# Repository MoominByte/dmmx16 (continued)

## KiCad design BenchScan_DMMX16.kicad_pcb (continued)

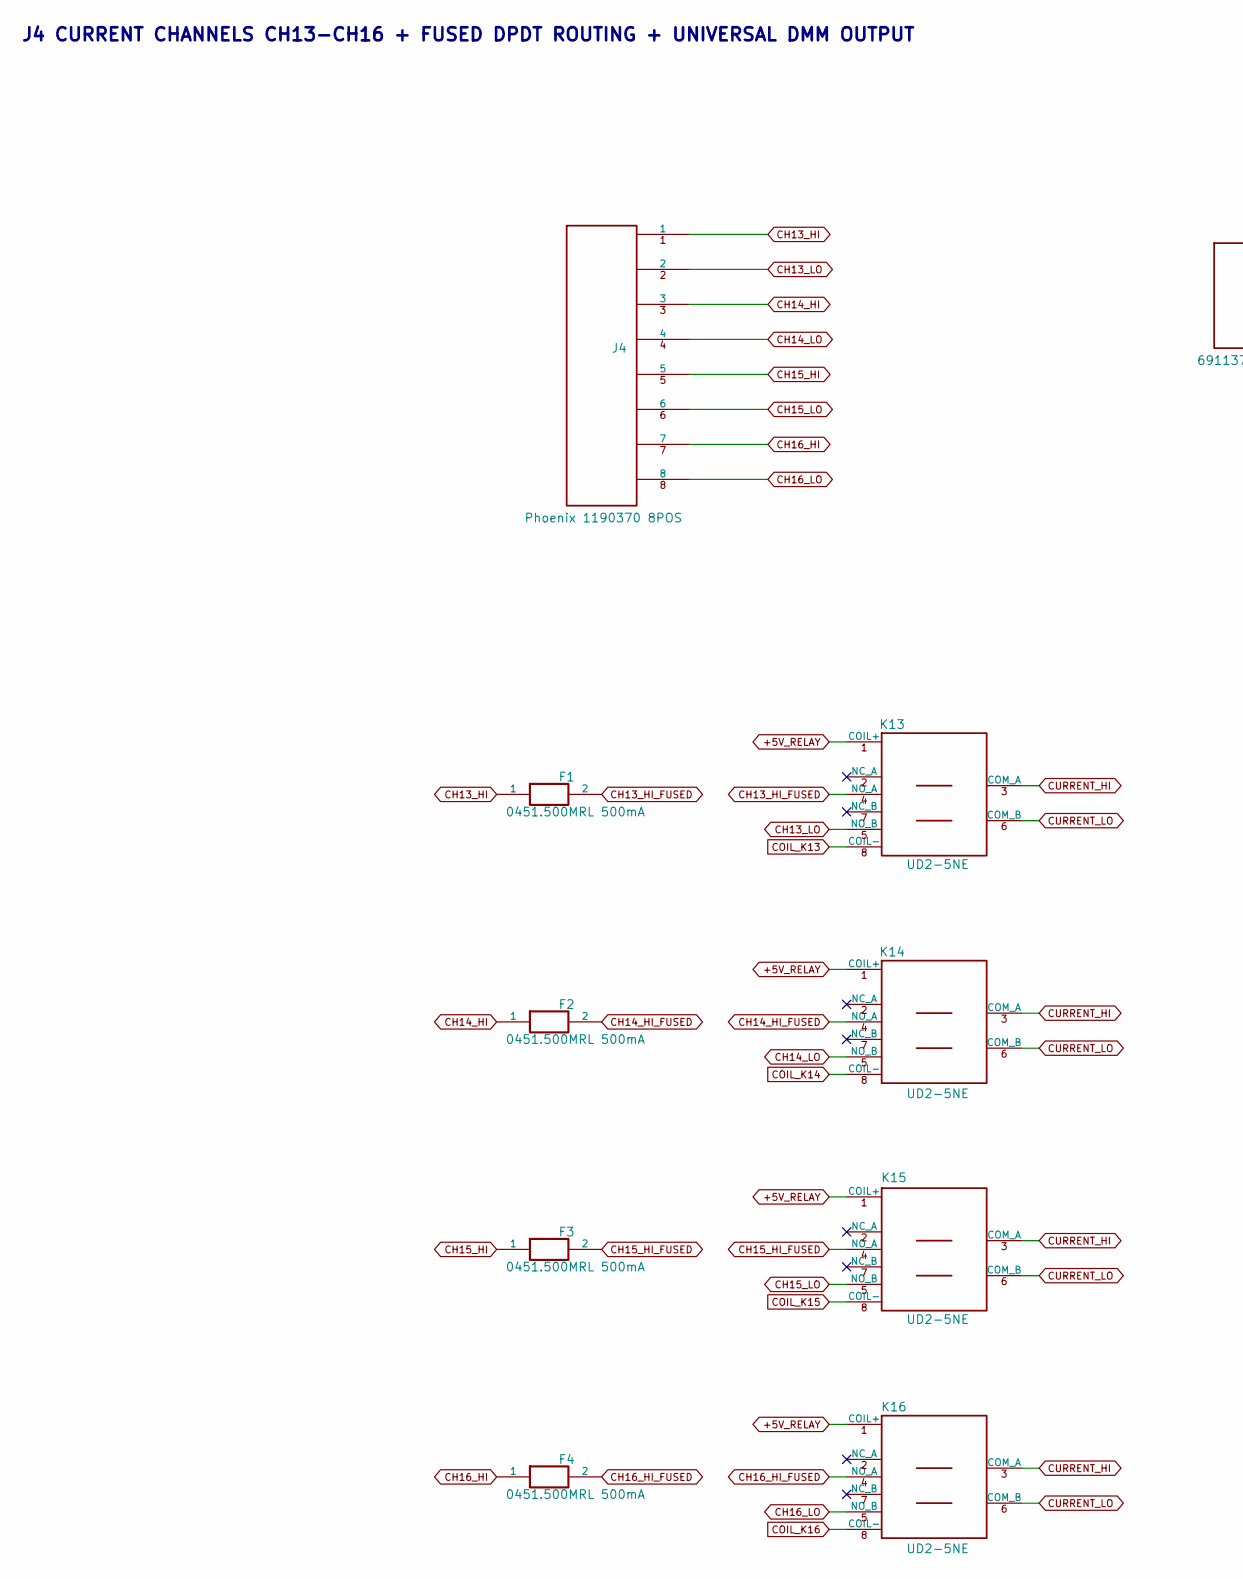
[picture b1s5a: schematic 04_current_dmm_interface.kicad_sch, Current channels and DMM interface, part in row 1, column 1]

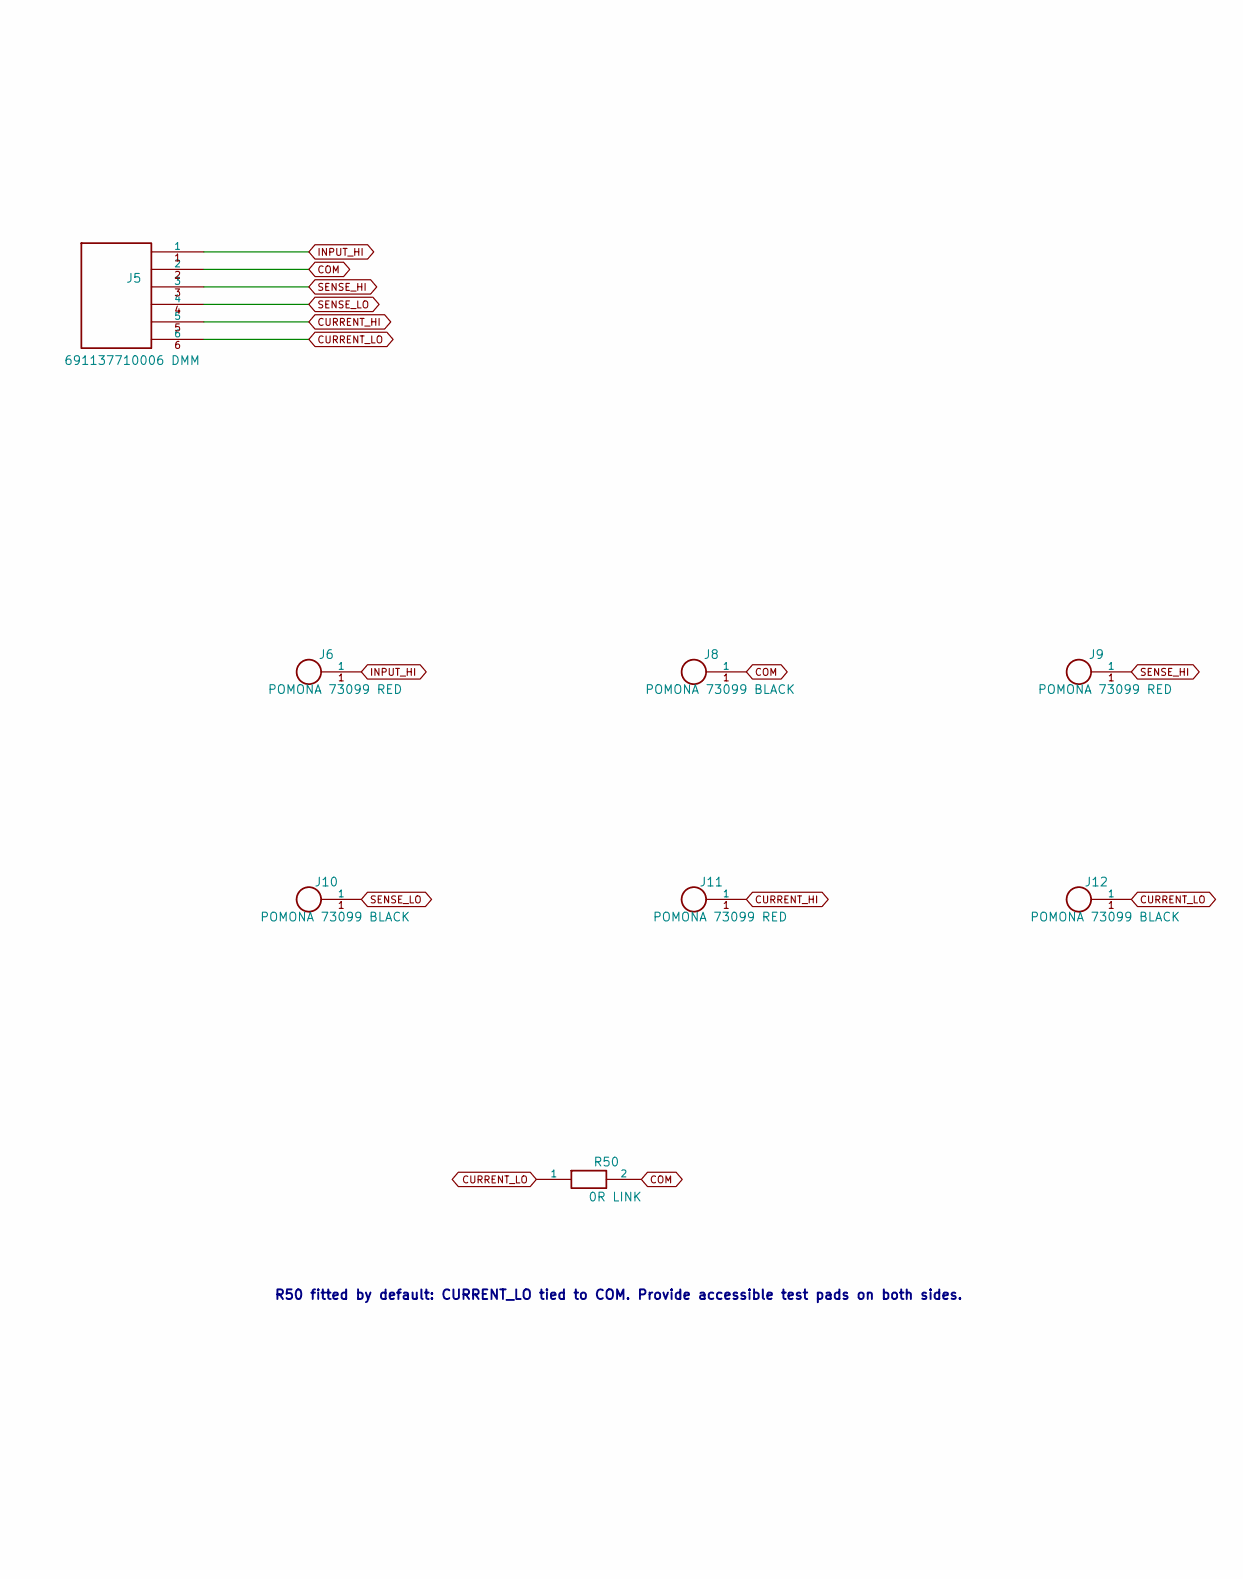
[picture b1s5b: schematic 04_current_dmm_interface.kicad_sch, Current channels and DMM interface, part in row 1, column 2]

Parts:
F1, F2, F3, F4: 0451.500MRL 500mA; Fuse_Littelfuse_0451_NANO2_2410
J4: Phoenix 1190370 8POS; Phoenix_1190370_LPTA-2.5-8-5.0_16THT_Paired
J5: 691137710006 DMM; J_Wurth_WR-TBL_691137710006
J6, J9, J11: POMONA 73099 RED; Pomona_73099_RightAngle_SafetyJack
J8, J10, J12: POMONA 73099 BLACK; Pomona_73099_RightAngle_SafetyJack
K13, K14, K15, K16: UD2-5NE; Relay_KEMET_UD2_NE
R50: 0R LINK; R_0805_2012Metric

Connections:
+5V_RELAY: K13.1 (COIL+), K14.1 (COIL+), K15.1 (COIL+), K16.1 (COIL+); also elsewhere on the board
CH13_HI: F1.1, J4.1
CH13_HI_FUSED: F1.2, K13.4 (NO_A)
CH13_LO: J4.2, K13.5 (NO_B)
CH14_HI: F2.1, J4.3
CH14_HI_FUSED: F2.2, K14.4 (NO_A)
CH14_LO: J4.4, K14.5 (NO_B)
CH15_HI: F3.1, J4.5
CH15_HI_FUSED: F3.2, K15.4 (NO_A)
CH15_LO: J4.6, K15.5 (NO_B)
CH16_HI: F4.1, J4.7
CH16_HI_FUSED: F4.2, K16.4 (NO_A)
CH16_LO: J4.8, K16.5 (NO_B)
COIL_K13: K13.8 (COIL-); also elsewhere on the board
COIL_K14: K14.8 (COIL-); also elsewhere on the board
COIL_K15: K15.8 (COIL-); also elsewhere on the board
COIL_K16: K16.8 (COIL-); also elsewhere on the board
COM: J5.2, J8.1, R50.2; also elsewhere on the board
CURRENT_HI: J5.5, J11.1, K13.3 (COM_A), K14.3 (COM_A), K15.3 (COM_A), K16.3 (COM_A)
CURRENT_LO: J5.6, J12.1, K13.6 (COM_B), K14.6 (COM_B), K15.6 (COM_B), K16.6 (COM_B), R50.1
INPUT_HI: J5.1, J6.1; also elsewhere on the board
SENSE_HI: J5.3, J9.1; also elsewhere on the board
SENSE_LO: J5.4, J10.1; also elsewhere on the board

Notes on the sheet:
R50 fitted by default: CURRENT_LO tied to COM. Provide accessible test pads on both sides.
J4 CURRENT CHANNELS CH13-CH16 + FUSED DPDT ROUTING + UNIVERSAL DMM OUTPUT

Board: 4 copper layers, 117 parts (0 on the bottom side), 106 nets, no tracks yet.

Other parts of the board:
H1, H2, H3, H4: MountingHole_3.20mm
